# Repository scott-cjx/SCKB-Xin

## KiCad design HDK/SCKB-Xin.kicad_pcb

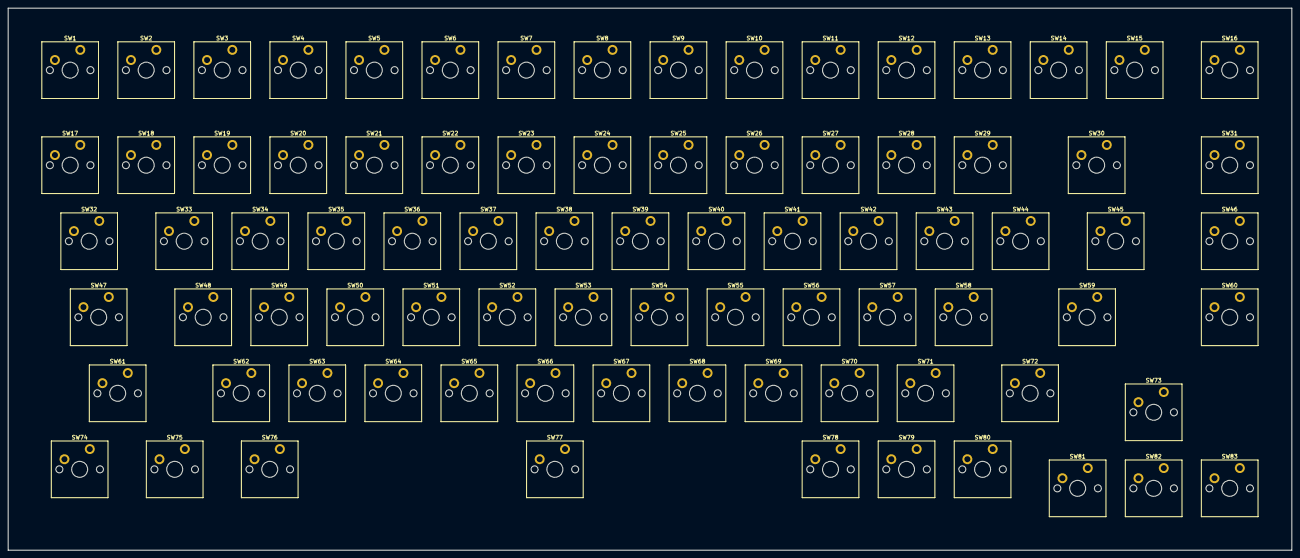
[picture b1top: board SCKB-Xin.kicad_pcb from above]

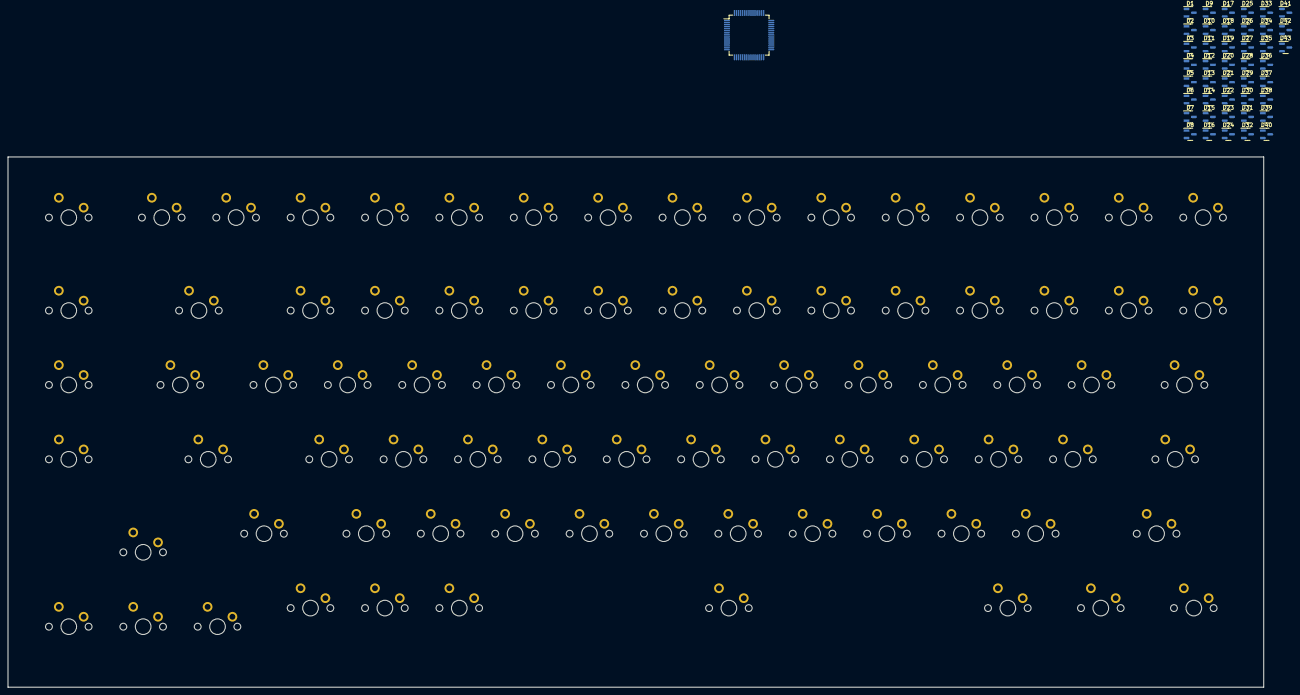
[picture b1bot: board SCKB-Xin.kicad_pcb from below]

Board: 2 copper layers, 321.6 x 135.8 mm, 127 parts (44 on the bottom side), 58 nets, no tracks yet.

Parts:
D1, D2, D3, D4, D5, D6, D7, D8, D9, D10, D11, D12, D13, D14, D15, D16, D17, D18, D19, D20, D21, D22, D23, D24, D25, D26, D27, D28, D29, D30, D31, D32, D33, D34, D35, D36, D37, D38, D39, D40, D41, D42, D43: D; SOT-23
SW1, SW2, SW3, SW4, SW5, SW6, SW7, SW8, SW9, SW10, SW11, SW12, SW13, SW14, SW15, SW16, SW17, SW18, SW19, SW20, SW21, SW22, SW23, SW24, SW25, SW26, SW27, SW28, SW29, SW30, SW31, SW32, SW33, SW34, SW35, SW36, SW37, SW38, SW39, SW40, SW41, SW42, SW43, SW44, SW45, SW46, SW47, SW48, SW49, SW50, SW51, SW52, SW53, SW54, SW55, SW56, SW57, SW58, SW59, SW60, SW61, SW62, SW63, SW64, SW65, SW66, SW67, SW68, SW69, SW70, SW71, SW72, SW73, SW74, SW75, SW76, SW77, SW78, SW79, SW80, SW81, SW82, SW83: SW_Push; SW_Cherry_MX_PCB_1.00u
U1: STM32F072RBTx; LQFP-64_10x10mm_P0.5mm

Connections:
/C0: SW1.1, SW16.1, SW17.1, SW31.1, SW32.1, SW46.1, SW47.1, SW60.1, SW61.1, SW74.1, SW83.1
/C1: SW2.1, SW15.1, SW18.1, SW33.1, SW48.1, SW75.1, SW82.1
/C6: SW7.1, SW10.1, SW23.1, SW26.1, SW38.1, SW41.1, SW53.1, SW56.1, SW66.1, SW69.1, SW77.1
/C7: SW8.1, SW9.1, SW24.1, SW25.1, SW39.1, SW40.1, SW54.1, SW55.1, SW67.1, SW68.1
/C10: SW6.1, SW11.1, SW22.1, SW27.1, SW37.1, SW42.1, SW52.1, SW57.1, SW65.1, SW70.1, SW78.1
/C11: SW5.1, SW12.1, SW21.1, SW28.1, SW36.1, SW43.1, SW51.1, SW58.1, SW64.1, SW71.1, SW79.1
/C12: SW4.1, SW13.1, SW20.1, SW29.1, SW35.1, SW44.1, SW50.1, SW59.1, SW63.1, SW72.1, SW80.1
/C13: SW3.1, SW14.1, SW19.1, SW30.1, SW34.1, SW45.1, SW49.1, SW62.1, SW73.1, SW76.1, SW81.1
/R0: D1.1 (K), D2.1 (K), D3.1 (K), D4.1 (K), D5.1 (K), D6.1 (K), D7.1 (K), D8.1 (K)
/R1: D9.1 (K), D10.1 (K), D11.1 (K), D12.1 (K), D13.1 (K), D14.1 (K), D15.1 (K), D16.1 (K)
/R2: D17.1 (K), D18.1 (K), D19.1 (K), D20.1 (K), D21.1 (K), D22.1 (K), D23.1 (K), D24.1 (K)
/R3: D25.1 (K), D26.1 (K), D27.1 (K), D28.1 (K), D29.1 (K), D30.1 (K), D31.1 (K)
/R4: D32.1 (K), D33.1 (K), D34.1 (K), D35.1 (K), D36.1 (K), D37.1 (K), D38.1 (K)
/R5: D39.1 (K), D40.1 (K), D41.1 (K), D42.1 (K), D43.1 (K)
unnamed: D1.2 (A), SW1.2
unnamed: D2.2 (A), SW3.2
unnamed: D3.2 (A), SW5.2
unnamed: D4.2 (A), SW7.2
unnamed: D5.2 (A), SW9.2
unnamed: D6.2 (A), SW11.2
unnamed: D7.2 (A), SW13.2
unnamed: D8.2 (A), SW15.2
unnamed: D9.2 (A), SW17.2
unnamed: D10.2 (A), SW19.2
unnamed: D11.2 (A), SW21.2
unnamed: D12.2 (A), SW23.2
unnamed: D13.2 (A), SW25.2
unnamed: D14.2 (A), SW27.2
unnamed: D15.2 (A), SW29.2
unnamed: D16.2 (A), SW31.2
unnamed: D17.2 (A), SW32.2
unnamed: D18.2 (A), SW34.2
unnamed: D19.2 (A), SW36.2
unnamed: D20.2 (A), SW38.2
unnamed: D21.2 (A), SW40.2
unnamed: D22.2 (A), SW42.2
unnamed: D23.2 (A), SW44.2
unnamed: D24.2 (A), SW46.2
unnamed: D25.2 (A), SW47.2
unnamed: D26.2 (A), SW49.2
unnamed: D27.2 (A), SW51.2
unnamed: D28.2 (A), SW53.2
unnamed: D29.2 (A), SW55.2
unnamed: D30.2 (A), SW57.2
unnamed: D31.2 (A), SW59.2
unnamed: D32.2 (A), SW61.2
unnamed: D33.2 (A), SW63.2
unnamed: D34.2 (A), SW65.2
unnamed: D35.2 (A), SW67.2
unnamed: D36.2 (A), SW69.2
unnamed: D37.2 (A), SW71.2
unnamed: D38.2 (A), SW73.2
unnamed: D39.2 (A), SW74.2
unnamed: D40.2 (A), SW76.2
unnamed: D41.2 (A), SW78.2
unnamed: D42.2 (A), SW80.2
unnamed: D43.2 (A), SW82.2
unnamed: U1.18 (VSS), U1.31 (VSS), U1.47 (VSS), U1.63 (VSS)

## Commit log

2024-02-17 Initialize gh-pages
2024-02-17 Moving files docs/* LICENSE using main
2024-02-17 Deploying to gh-pages from @ scott-cjx/SCKB-Xin@ac64af7eca95d2c27b3345cbb5406b741f859e64 🚀
2024-02-17 added kle
2024-02-17 Deploying to gh-pages from @ scott-cjx/SCKB-Xin@365df66bf6d3ffe6cd40ad28d6908f416ea6af1f 🚀
2024-02-17 init commit
2024-02-17 Deploying to gh-pages from @ scott-cjx/SCKB-Xin@bb52f0238d5cff857cdc6bd2c32fe63f0896f5d2 🚀
2024-10-07 Deploying to gh-pages from @ scott-cjx/SCKB-Xin@512104f37a26dae144e94e274be625fec5cce8e9 🚀
